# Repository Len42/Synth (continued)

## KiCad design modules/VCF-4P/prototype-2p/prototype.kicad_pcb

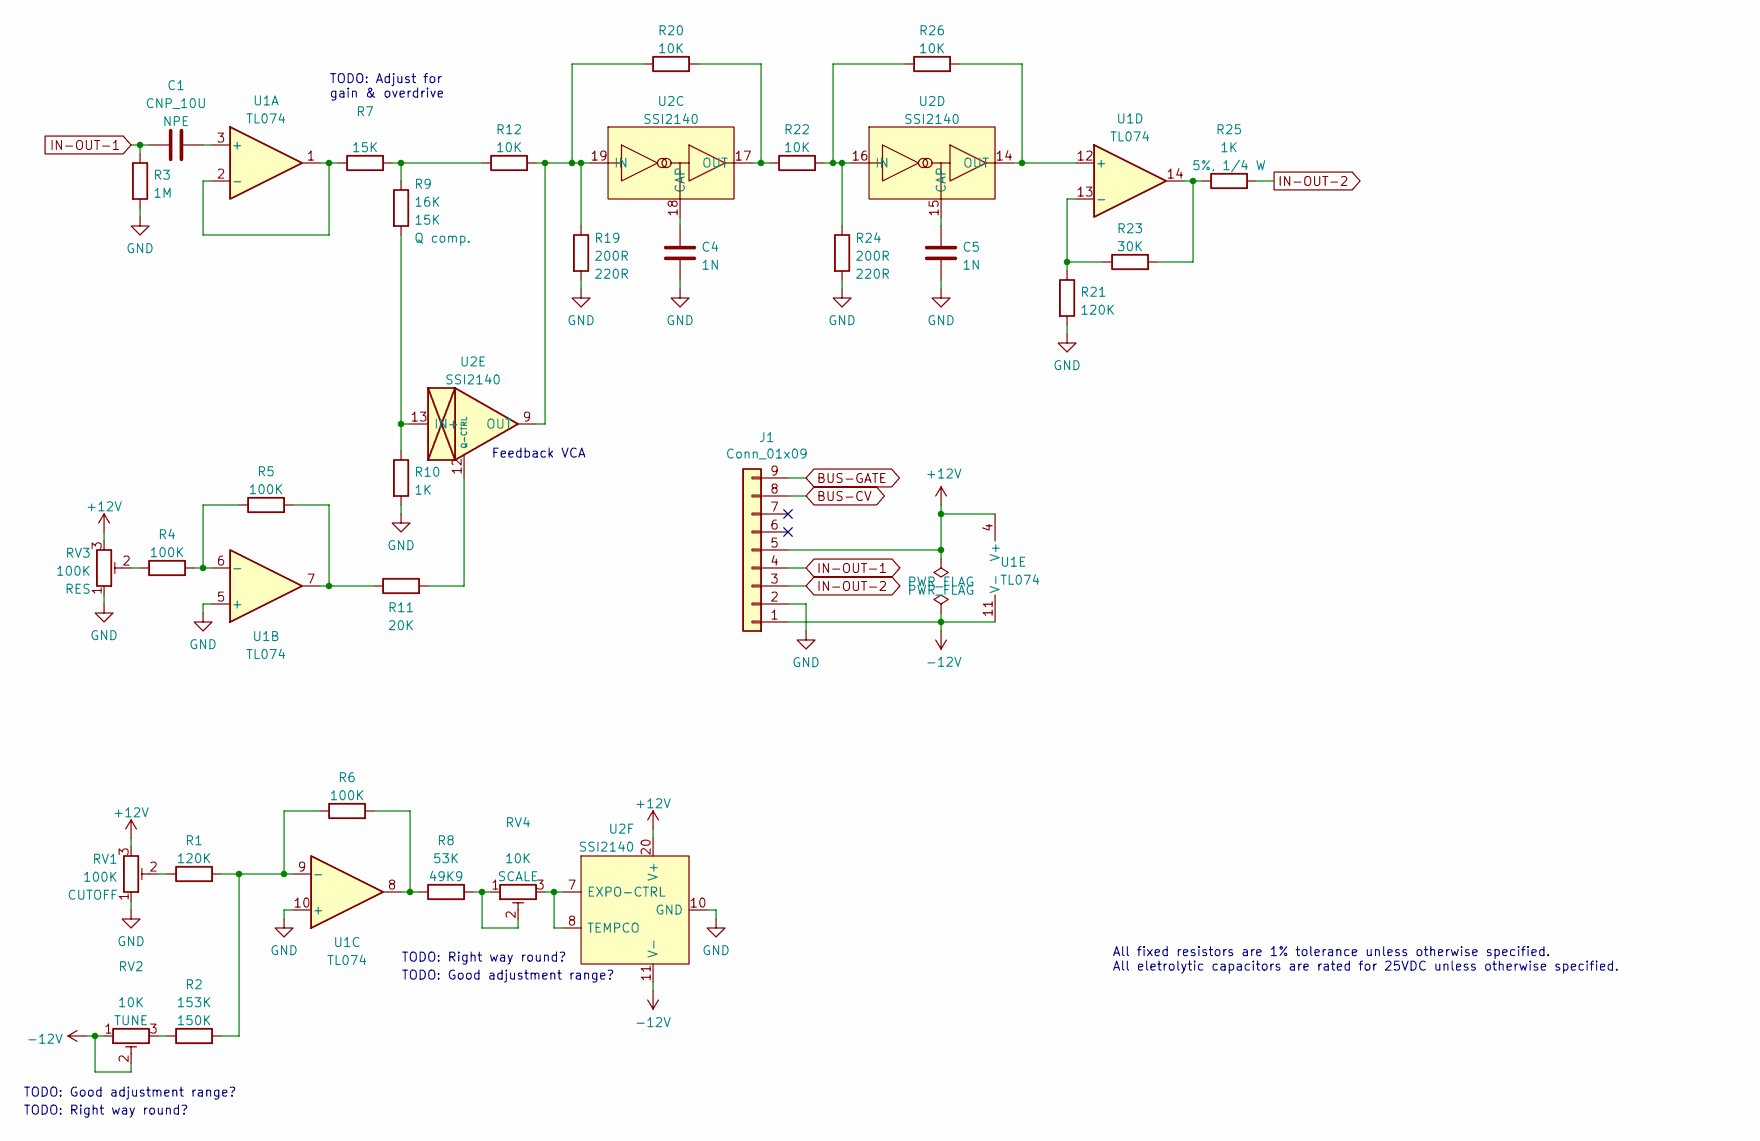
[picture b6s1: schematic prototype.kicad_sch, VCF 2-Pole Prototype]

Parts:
C1: CNP_10U; C_Radial_D5.0mm_H5.0mm_P2.50mm; ManufacturerPartNum ECE-A1EN100UI
C4, C5: 1N; C_Rect_Kemet_L7.2mm_W2.5mm_P5mm
J1: Conn_01x09; PinHeader_1x09_P2.54mm_Vertical
R1, R21: 120K; R_Axial_DIN0207_L6.3mm_D2.5mm_P7.62mm_Horizontal; ManufacturerPartNum MFR-12*
R2: 153K; R_Axial_DIN0207_L6.3mm_D2.5mm_P7.62mm_Horizontal; ManufacturerPartNum MFR-12*
R3: 1M; SB_Gen_1; ManufacturerPartNum MFR-12*
R4: 100K; SB_Gen_4; ManufacturerPartNum MFR-12*
R5, R6: 100K; SB_Gen_1; ManufacturerPartNum MFR-12*
R7: ManufacturerPartNum MFR-12*
R8: 53K; R_Axial_DIN0207_L6.3mm_D2.5mm_P7.62mm_Horizontal; ManufacturerPartNum MFR-12*
R9: 16K; R_Axial_DIN0207_L6.3mm_D2.5mm_P7.62mm_Horizontal; ManufacturerPartNum MFR-12*
R10: 1K; SB_Gen_1; ManufacturerPartNum MFR-12*
R11: 20K; SB_Gen_1; ManufacturerPartNum MFR-12*
R12: 10K; R_Axial_DIN0207_L6.3mm_D2.5mm_P7.62mm_Horizontal; ManufacturerPartNum MFR-12*
R19, R24: 200R; SB_Gen_1; ManufacturerPartNum MFR-12*
R20, R26: 10K; SB_Gen_2; ManufacturerPartNum MFR-12*
R22: 10K; SB_Gen_1; ManufacturerPartNum MFR-12*
R23: 30K; SB_Gen_1; ManufacturerPartNum MFR-12*
R25: 1K; SB_Gen_2; ManufacturerPartNum CCF071K00JKE36
RV1, RV3: 100K; Potentiometer_Bourns_3310R_Top; ManufacturerPartNum 3386*
RV2, RV4: ManufacturerPartNum 3386*
U1: TL074; DIP-14_W7.62mm; ManufacturerPartNum TL074BCN
U2: SSI2140; Breakout_DIP-20_W15.24mm; ManufacturerPartNum SSI2140

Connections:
+12V: J1.5, RV1.3, RV3.3, U1.4 (V+), U2.20 (V+)
-12V: J1.1, RV2.1, RV2.2, U1.11 (V-), U2.11 (V-)
BUS-CV: J1.8
BUS-GATE: J1.9
GND: C4.2, C5.2, J1.2, R3.2, R10.2, R19.2, R21.2, R24.2, RV1.1, RV3.1, U1.5 (+), U1.10 (+), U2.10 (GND)
IN-OUT-1: C1.1, J1.4, R3.1
IN-OUT-2: J1.3, R25.2
unnamed: C1.2, U1.3 (+)
unnamed: C4.1, U2.18 (CAP)
unnamed: C5.1, U2.15 (CAP)
unnamed: R1.1, RV1.2
unnamed: R1.2, R2.2, R6.1, U1.9 (-)
unnamed: R2.1, RV2.3
unnamed: R4.1, RV3.2
unnamed: R4.2, R5.1, U1.6 (-)
unnamed: R6.2, R8.1, U1.8
unnamed: R7.1, U1.1, U1.2 (-)
unnamed: R8.2, RV4.1, RV4.2
unnamed: R9.2, R10.1, U2.13 (IN+)
unnamed: R5.2, R11.1, U1.7
unnamed: R11.2, U2.12 (Q-CTRL)
unnamed: R7.2, R9.1, R12.1
unnamed: R12.2, R19.1, R20.1, U2.9 (OUT), U2.19 (IN)
unnamed: R20.2, R22.1, U2.17 (OUT)
unnamed: R21.1, R23.1, U1.13 (-)
unnamed: R22.2, R24.1, R26.1, U2.16 (IN)
unnamed: R23.2, R25.1, U1.14
unnamed: R26.2, U1.12 (+), U2.14 (OUT)
unnamed: RV4.3, U2.7 (EXPO-CTRL), U2.8 (TEMPCO)

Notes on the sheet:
TODO: Good adjustment range?
TODO: Adjust for gain & overdrive
TODO: Right way round?
All fixed resistors are 1% tolerance unless otherwise specified. All eletrolytic capacitors are rated for 25VDC unless otherwise specified.
Feedback VCA

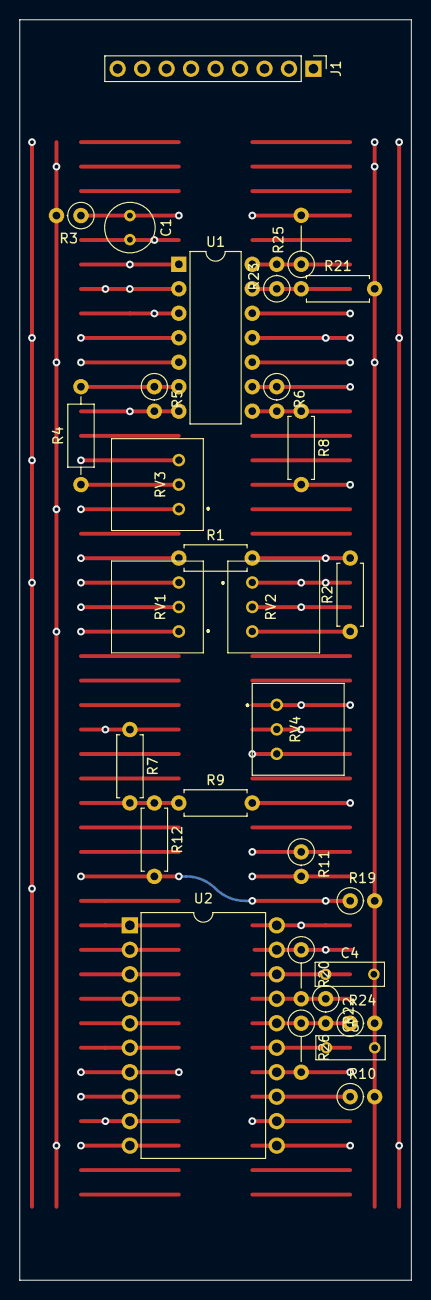
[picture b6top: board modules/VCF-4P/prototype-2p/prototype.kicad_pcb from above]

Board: 6 copper layers, 40.6 x 130.8 mm, 30 parts (0 on the bottom side), 27 nets.

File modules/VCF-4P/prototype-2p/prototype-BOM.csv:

Ref,Qty,Value,Value2,Note,Description,Datasheet,Manufacturer,ManuPartNum,Distributor1,DistributorPartNum1,DistributorPartLink1,Distributor2,DistributorPartNum2,DistributorPartLink2,Distributor3,DistributorPartNum3,DistributorPartLink3
"C1","1","CNP_10U","NPE","","Capacitor - Non-polarized Electrolytic","https://www.mouser.ca/datasheet/2/315/ABA0000C1053-947510.pdf","Panasonic","ECE-A1EN100UI","Mouser","667-ECE-A1EN100UI","https://www.mouser.ca/ProductDetail/Panasonic/ECE-A1EN100UI?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","","","","","",""
"C4 C5","2","1N","","","Capacitor - Film","","","","","","","","","","","",""
"J1","1","Conn_01x09","","","Generic connector, single row, 01x09, script generated (kicad-library-utils/schlib/autogen/connector/)","","","","","","","","","","","",""
"R1 R21","2","120K","1%, 1/6 W","","Resistor","https://www.mouser.ca/datasheet/2/447/Yageo_LR_MFR_1-1714151.pdf","YAGEO","MFR-12*","Mouser","603-MFR-12*","https://www.mouser.ca/c/?m=YAGEO&power+rating=166+mW+(1%2f6+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","","","","","",""
"R2","1","153K","150K","","Resistor","https://www.mouser.ca/datasheet/2/447/Yageo_LR_MFR_1-1714151.pdf","YAGEO","MFR-12*","Mouser","603-MFR-12*","https://www.mouser.ca/c/?m=YAGEO&power+rating=166+mW+(1%2f6+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","","","","","",""
"R3","1","1M","1%, 1/6 W","","Resistor","https://www.mouser.ca/datasheet/2/447/Yageo_LR_MFR_1-1714151.pdf","YAGEO","MFR-12*","Mouser","603-MFR-12*","https://www.mouser.ca/c/?m=YAGEO&power+rating=166+mW+(1%2f6+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","","","","","",""
"R4 R5 R6","3","100K","1%, 1/6 W","","Resistor","https://www.mouser.ca/datasheet/2/447/Yageo_LR_MFR_1-1714151.pdf","YAGEO","MFR-12*","Mouser","603-MFR-12*","https://www.mouser.ca/c/?m=YAGEO&power+rating=166+mW+(1%2f6+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","","","","","",""
"R7","1","24K","15K","","Resistor","https://www.mouser.ca/datasheet/2/447/Yageo_LR_MFR_1-1714151.pdf","YAGEO","MFR-12*","Mouser","603-MFR-12*","https://www.mouser.ca/c/?m=YAGEO&power+rating=166+mW+(1%2f6+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","","","","","",""
"R8","1","53K","49K9","","Resistor","https://www.mouser.ca/datasheet/2/447/Yageo_LR_MFR_1-1714151.pdf","YAGEO","MFR-12*","Mouser","603-MFR-12*","https://www.mouser.ca/c/?m=YAGEO&power+rating=166+mW+(1%2f6+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","","","","","",""
"R9","1","16K","15K","Q comp.","Resistor","https://www.mouser.ca/datasheet/2/447/Yageo_LR_MFR_1-1714151.pdf","YAGEO","MFR-12*","Mouser","603-MFR-12*","https://www.mouser.ca/c/?m=YAGEO&power+rating=166+mW+(1%2f6+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","","","","","",""
"R10","1","1K","1%, 1/6 W","","Resistor","https://www.mouser.ca/datasheet/2/447/Yageo_LR_MFR_1-1714151.pdf","YAGEO","MFR-12*","Mouser","603-MFR-12*","https://www.mouser.ca/c/?m=YAGEO&power+rating=166+mW+(1%2f6+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","","","","","",""
"R11","1","20K","1%, 1/6 W","","Resistor","https://www.mouser.ca/datasheet/2/447/Yageo_LR_MFR_1-1714151.pdf","YAGEO","MFR-12*","Mouser","603-MFR-12*","https://www.mouser.ca/c/?m=YAGEO&power+rating=166+mW+(1%2f6+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","","","","","",""
"R12 R20 R22 R26","4","10K","1%, 1/6 W","","Resistor","https://www.mouser.ca/datasheet/2/447/Yageo_LR_MFR_1-1714151.pdf","YAGEO","MFR-12*","Mouser","603-MFR-12*","https://www.mouser.ca/c/?m=YAGEO&power+rating=166+mW+(1%2f6+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","","","","","",""
"R19 R24","2","200R","220R","","Resistor","https://www.mouser.ca/datasheet/2/447/Yageo_LR_MFR_1-1714151.pdf","YAGEO","MFR-12*","Mouser","603-MFR-12*","https://www.mouser.ca/c/?m=YAGEO&power+rating=166+mW+(1%2f6+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","","","","","",""
"R23","1","30K","1%, 1/6 W","","Resistor","https://www.mouser.ca/datasheet/2/447/Yageo_LR_MFR_1-1714151.pdf","YAGEO","MFR-12*","Mouser","603-MFR-12*","https://www.mouser.ca/c/?m=YAGEO&power+rating=166+mW+(1%2f6+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","","","","","",""
"R25","1","1K","5%, 1/4 W","Output limiting","Resistor","https://www.mouser.ca/datasheet/2/427/ccf07-1762725.pdf","Vishay / Dale","CCF071K00JKE36","Mouser","71-CCF071K00JKE36","https://www.mouser.ca/ProductDetail/Vishay-Dale/CCF071K00JKE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","","","","","",""
"RV1 RV3","2","100K","","","Trim-potentiometer","https://www.mouser.ca/datasheet/2/54/3386-776606.pdf","Bourns","3386*","Mouser","652-3386*","https://www.mouser.ca/c/passive-components/resistors/variabl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","","","","","",""
"RV2 RV4","2","5K","10K","","Trim-potentiometer","https://www.mouser.ca/datasheet/2/54/3386-776606.pdf","Bourns","3386*","Mouser","652-3386*","https://www.mouser.ca/c/passive-components/resistors/variabl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","","","","","",""
"U1","1","TL074","","","Quad Low-Noise JFET-Input Operational Amplifiers, DIP-14/SOIC-14","http://www.ti.com/lit/ds/symlink/tl071.pdf","Texas Instruments","TL074BCN","Mouser","595-TL074BCN","https://www.mouser.ca/ProductDetail/?qs=vxEfx8VrU7BHurOY5iQd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","","","","","",""
"U2","1","SSI2140","","","Voltage Controlled Filter (VCF), SSOP-20","http://soundsemiconductor.com/downloads/ssi2140datasheet.pdf","Sound Semiconductor","SSI2140","Antique Electronic Supply","P-Q-SSI2140","https://www.tubesandmore.com/products/integrated-circuit-ssi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","SynthCube","ICSMSSI2140","https://synthcube.com/cart/ics-and-semiconductors/sound-semi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","Thonk","SSI2140","https://www.thonk.co.uk/shop/sound-semiconductor/"
